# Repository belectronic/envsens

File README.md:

# EnvSens

EnvSens is a compact sensor module for ambient air and brightness monitoring with an ESP-12E Wifi microcontroller.
It runs until a minimal battery voltage from 2.5 V properly. Ideal for IoT applications!

With help of the BME680 sensor from Bosch, temperature, humidity, air pressure and air quality can be measured in a very energy-saving way.
In addition, LITE-ON's LTR303 digital ambient light sensor enables the monitoring of daylight and lamp light close to the spectral viewing range.
A real-time clock (RTC) AB0805 from Abracon provides the time for the measuring points with low power consumption.
All modules are connected to ESP-12E via I2C bus.

---

## Hardware

| Module | Function | Datasheet | Software Library |
| - | - | - | - |
| Bosch BME680 | Temperature, Humidity, Pressure, Air Quality | [bst-bme680-ds001.pdf](https://www.bosch-sensortec.com/media/boschsensortec/downloads/datasheets/bst-bme680-ds001.pdf) | [Adafruit_BME680](https://github.com/adafruit/Adafruit_BME680) |
| LITE-ON LTR303 | Ambient Light Sensor | [Lite-On_LTR-303ALS-01_DS.pdf](https://www.mouser.com/datasheet/2/239/Lite-On_LTR-303ALS-01_DS_ver%201.1-1175269.pdf)| [Automote_LTR303](https://github.com/automote/LTR303) |
| Abracon AB0805 | RTC | [AB08X5-RTC.PDF](https://abracon.com/Precisiontiming/AB08X5-RTC.PDF ) | [AB0805_lib (*)](https://github.com/curransinha/AB0805_lib) |
| AI-Thinker ESP-12E | 32 Bit Microcontroller with WiFi | [ESP12E_Datasheet.pdf](https://components101.com/sites/default/files/component_datasheet/ESP12E%20Datasheet.pdf) |
| * Issue in Abracon AB0805 Library: Hours shows 0 every time. Resolution -> Remove all functions for 12-hour format (see issues discussions) |

---

## Pinout

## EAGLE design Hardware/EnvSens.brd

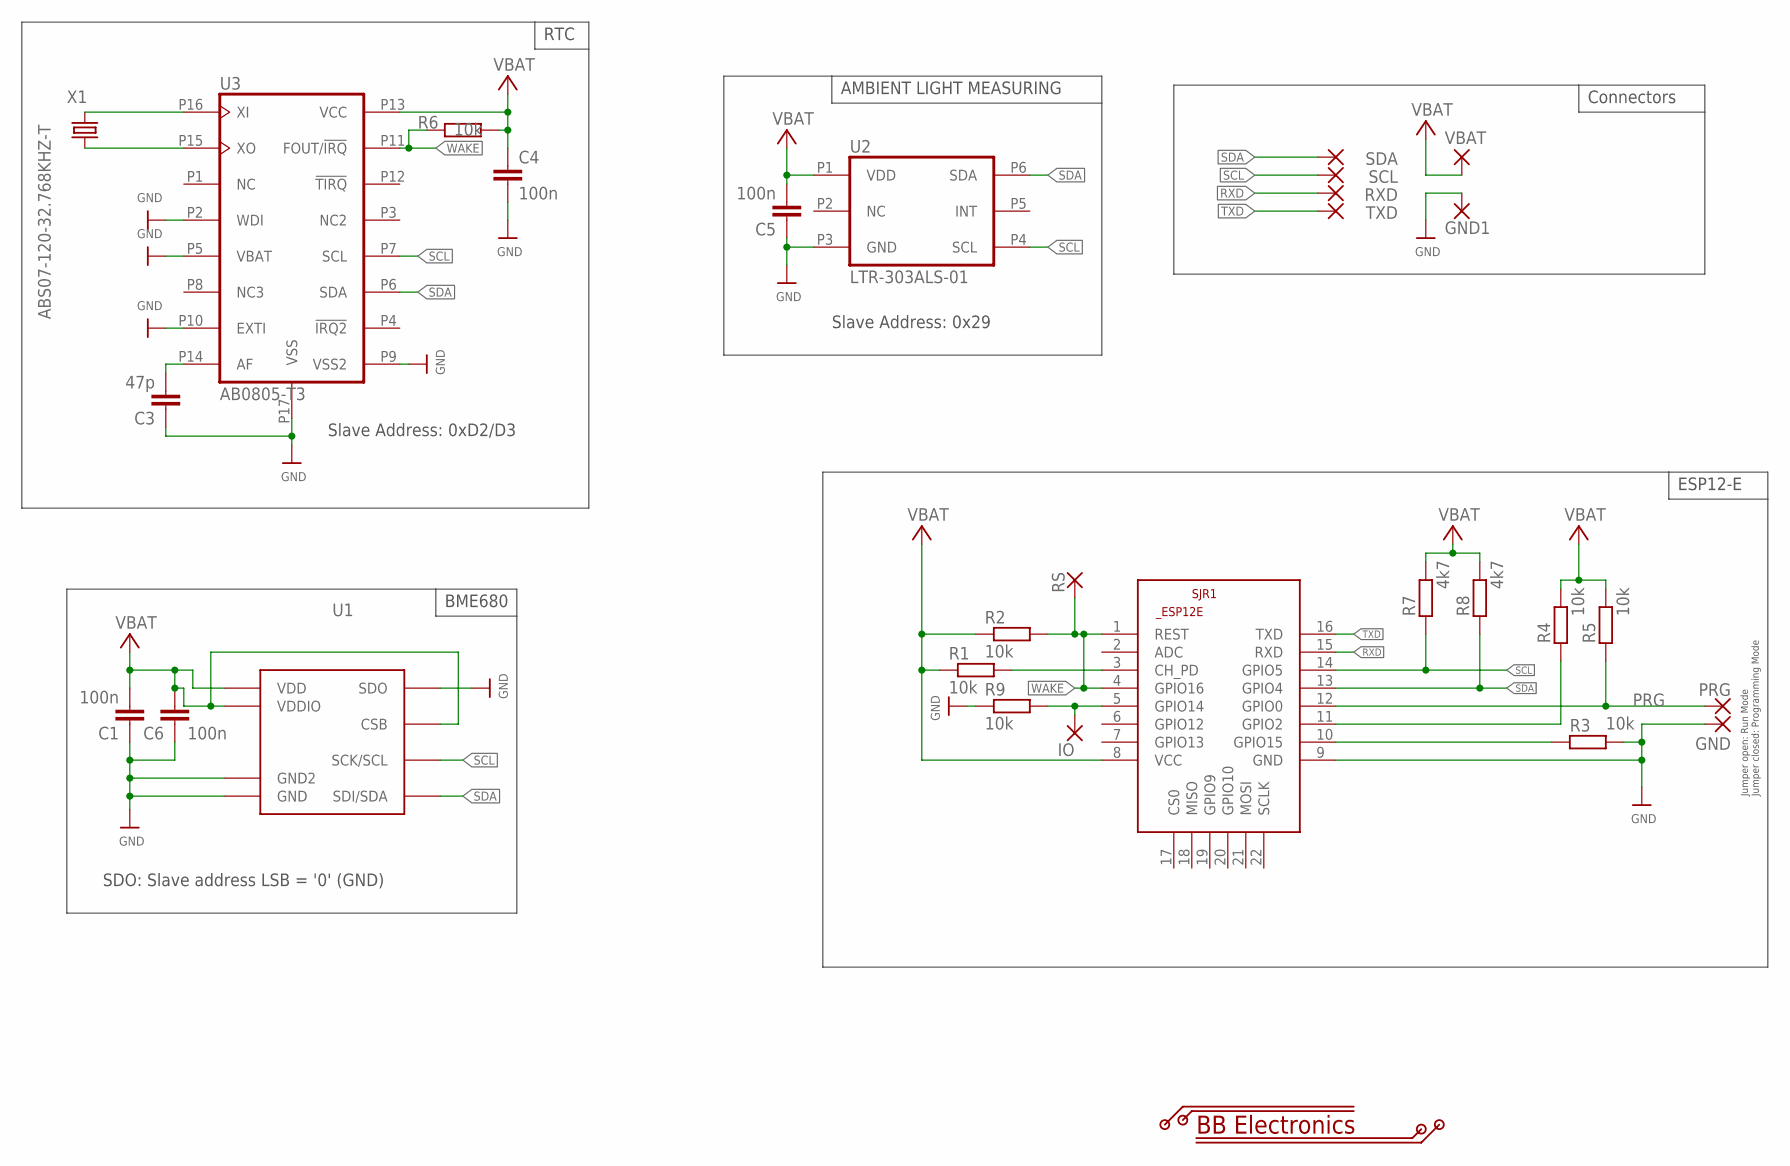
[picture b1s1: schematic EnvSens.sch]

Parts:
C1, C4, C5, C6: 100n; 0603
C3: 47p; 0603
GND: SMD2; SMD1,27-2,54
GND1: SMD5; SMD2,54-5,08
IO: SMD2; SMD1,27-2,54
PRG: SMD2; SMD1,27-2,54
R1, R2, R3, R4, R5, R6, R9: 10k; 0603
R7, R8: 4k7; 0603
RS: SMD2; SMD1,27-2,54
RXD: SMD2; SMD1,27-2,54
SCL: SMD2; SMD1,27-2,54
SDA: SMD2; SMD1,27-2,54
SJR1: ESP8266-12EESP12E; ESP8266-ESP12E
TXD: SMD2; SMD1,27-2,54
U1: BME680
U2: LTR-303ALS-01; 6-DFN
U3: AB0805-T3; 16-VFQFN
VBAT: SMD5; SMD2,54-5,08
X1: ABS07-120-32.768KHZ-T

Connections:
GND: C1.P1 (1), C3.P1 (1), C4.P2 (2), C5.P1 (1), C6.P1 (1), GND.1, GND1.1, R3.P2 (2), R9.P1 (1), SJR1.9 (GND), U1.P1 (GND), U1.P5 (SDO), U1.P7 (GND2), U2.P3 (GND), U3.P2 (WDI), U3.P5 (VBAT), U3.P9 (VSS2), U3.P10 (EXTI), U3.P17 (VSS)
GPIO: IO.1, R9.P2 (2), SJR1.5 (GPIO14)
unnamed: R1.P2 (2), SJR1.3 (CH_PD)
unnamed: R3.P1 (1), SJR1.10 (GPIO15)
unnamed: R4.P1 (1), SJR1.11 (GPIO2)
unnamed: C3.P2 (2), U3.P14 (AF)
unnamed: U3.P16 (XI), X1.P2 (2)
unnamed: U3.P15 (XO), X1.P1 (1)
PRG: PRG.1, R5.P1 (1), SJR1.12 (GPIO0)
RXD: RXD.1, SJR1.15 (RXD)
SCL: R7.P1 (1), SCL.1, SJR1.14 (GPIO5), U1.P4 (SCK/SCL), U2.P4 (SCL), U3.P7 (SCL)
SDA: R8.P1 (1), SDA.1, SJR1.13 (GPIO4), U1.P3 (SDI/SDA), U2.P6 (SDA), U3.P6 (SDA)
TXD: SJR1.16 (TXD), TXD.1
VBAT: C1.P2 (2), C4.P1 (1), C5.P2 (2), C6.P2 (2), R1.P1 (1), R2.P1 (1), R4.P2 (2), R5.P2 (2), R6.P2 (2), R7.P2 (2), R8.P2 (2), SJR1.8 (VCC), U1.P2 (CSB), U1.P6 (VDDIO), U1.P8 (VDD), U2.P1 (VDD), U3.P13 (VCC), VBAT.1
WAKE: R2.P2 (2), R6.P1 (1), RS.1, SJR1.1 (REST), SJR1.4 (GPIO16), U3.P11 (FOUT/!IRQ!)

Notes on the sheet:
SDO: Slave address LSB = '0' (GND)
Jumper open: Run Mode Jumper closed: Programming Mode
BME680
RTC
AMBIENT LIGHT MEASURING
Connectors
ESP12-E
Slave Address: 0xD2/D3
Slave Address: 0x29

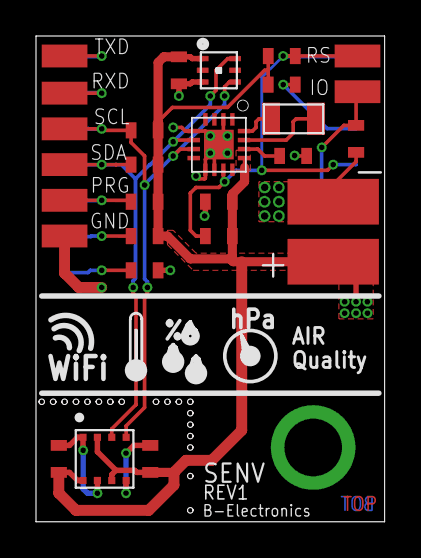
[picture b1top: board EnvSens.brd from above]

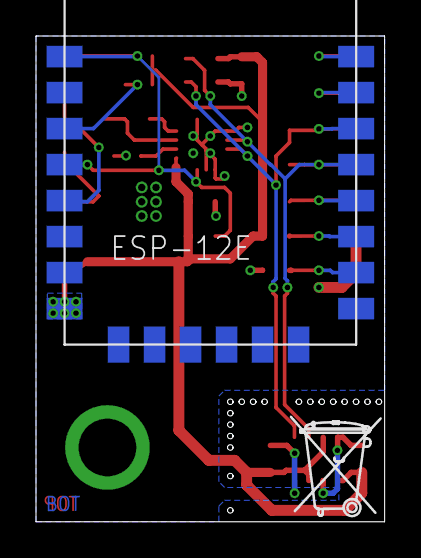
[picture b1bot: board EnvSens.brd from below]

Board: 2 copper layers, 19.4 x 27.0 mm, 30 parts (2 on the bottom side), 15 nets.

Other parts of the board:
U$5: TONNE_10.00

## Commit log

2022-01-20 Add all files
2022-01-20 Fix wake up issue
2022-11-25 Create LICENSE
